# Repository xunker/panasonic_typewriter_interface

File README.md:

# Panasonic Typewriter Interface

https://github.com/xunker/panasonic_typewriter_interface

Print text using the Interface Port of your compatible Panasonic KX-R Daisywheel
typewriter, KX-W word processor, RK-T "CupWheel" typewriter, or KX-WD55
daisywheel printer. Emulates the serial/RS-232 function of the KX-R60 (currently
working), and RP-K100/RP-K105 (in development) interface adapters.

Use your 🏋️heavy🥌 and 🐢slow🐌 typewriter as a noisy, inconvenient, inflexible,
single-page printer!

A complete video of the ~~high~~ low-speed daisywheel action can be found on [the TouYubes](https://youtu.be/Eb-3h6uFz88).

## Table of Contents

- [Compatibility](#compatibility)
- [Typewriter Pinout](#typewriter-pinout)
- [Arduino Wiring](#arduino-wiring)
- [Code](#code)
- [Printerering (aka, how to use this)](#printerering-aka-how-to-use-this)
- [Serial Configuration Terminal](#serial-configuration-terminal)
- [Known Problems](#known-problems)
- [Theory of Operation](#theory-of-operation)
- [TODO](#todo)
- [License](#license)

## Compatibility

### KX-R series with MiniDIN-8 port

Developed and tested with my KX-R435, and should be compatible with any other
Panasonic typewriter with the round, 8-pin MiniDIN port.

### KX-W series with DE-9 port

Untested, but should work with machines which have a DE-9 (DB-9) connector.
**Currently does not work**, but is in active development. See
[rp-k10x_vs_kx-r60.md](./rp-k10x_vs_kx-r60.md) for research details.

## Typewriter Pinout

See [PINOUT.md](./PINOUT.md) for detailed information about the typewriter
connector pinout.

## Arduino Wiring

Although this is built around the Arduino Nano, any 5V board which uses the
ATmega328 will also work. Any other 5V ATmega MCU should work as as well (such
as the ATmega32U4in the Arduino Micro), and clones like the LGT8F328 (tested).

Non-ATmega/AVR boards *may* work, as long as they are compatible with the
libraries used in this project (see "Required Libraries"), have enough pins,
and run on 5V (or are 5V-tolerant). I have not tried any of this.

### Adapter Board

There's an [adapter board](adapter_boards/README.md) available to ease assembly,
and to provide additional features.

### Connecting Arduino to Typewriter without Adapter Board

Minimum required:

Arduino Pin | Goes To                | Purpose
------------|------------------------|--------
A0          | Typewriter ON_LINE pin | ~ON_LINE signal to typewriter
A1          | Typewriter TXD_PIN pin | TXD_PIN signal to typewriter
A2          | Typewriter STB_PIN pin | ~STB_PIN signal to typewriter
A3          | Typewriter ACK_PIN pin | ~ACK_PIN signal from typewriter
A6          | Switch to ground       | "RUN/HALT" switch (GO_PIN), active low

Optional "Mode" button:

Arduino Pin | Goes To          | Purpose
------------|------------------|--------
A7          | Button to ground | Mode button (MODE_PIN), optional, active low

Separate USB-to-Serial Adapter: You can use the built-in USB port as the Serial
connection, but hardware flow control will not be available. To use hardware
flow control you will need to connect up to an external USB to Serial adapter:

Arduino Pin | Goes To                  | Purpose
------------|--------------------------|--------
TX1 (D1)    | RxD on USB Serial Module | Transmit serial data to USB host
RX0 (D0)    | TxD on USB Serial Module | Receive serial data from USB host
11          | CTS on USB Serial module | CTS (Clear to Send)
12          | RTS on USB Serial module | RTS (Request to Send)

You can also connect some optional additional LEDs for debugging (or because
they look neat when they blink):

Arduino Pin | Goes To | Purpose
------------|---------|--------
8           | LED +   | State of ON_LINE pin
6           | LED +   | State of STB_LED pin
2           | LED +   | State of ACK_LED pin
3           | LED +   | State of TXD_LED pin

## Code

The included code will read data from the `Serial` device (usually USB Serial)
and relay that to the typewriter in the correct format.

### Required Libraries

The following libraries are required by default. They can either be installed
manually or via the Arduino IDE:

* [SerialCmd](https://github.com/gpb01/SerialCmd)
* [MemoryUsage](https://github.com/Locoduino/MemoryUsage)
* [AceButton](https://github.com/bxparks/AceButton/)

SerialCmd and MemoryUsage are only needed by the
[Serial Configuration Terminal](./SERIAL_CONFIG.md) (enabled default). AceButton
is only needed if the "Mode" button is enabled (enabled by default).

### Configure

NOTE: if you are using the included [adapter board](adapter_boards/README.md), you do not need to do any
additional configuration. Simply connect your cable and adjust the "Cable Type"
jumpers so they are both closest to whichever LED (D1 or D2) is lit up.

Edit [panasonic_typewriter_interface.ino](./panasonic_typewriter_interface.ino)
and change the following lines as appropriate:

```c
#define ON_LINE_PIN A0 // Output, active LOW
#define STB_PIN     A2 // Output, active LOW
#define ACK_PIN     A3 // Input, active LOW
#define TXD_PIN     A1 // Output; HIGH = 1, LOW = 0

#define GO_PIN      A6 // trigger printing to begin when this is pulled low

#define MODE_PIN    A7 // trigger printing to begin when this is pulled low

/* RTS_PIN/CTS_PIN are only needed if `#define ENABLE_RTS_CTS` is uncommented */
#define RTS_PIN 12 // incoming from RTS, active low (for ENABLE_RTS_CTS)
#define CTS_PIN 11 // outgoing to CTS, active low   (for ENABLE_RTS_CTS)
```

CHECK WHAT KIND OF CABLE YOU HAVE, and remember that a Macintosh-style printer
cable likely has several pins swapped.

Once you're done, upload it to your Arduino-compatible MCU.

There is also a "Demo Mode" that will just print text automatically and not
wait for input over serial; enable that by uncommenting `// #define TEST_MODE`
in panasonic_typewriter_interface.ino.

#### Extra LEDs (Optional, default)

By default, there are 4 addition LEDs broken out to show the status of each of
the signal lines (in addition to the built-in LED).

```c
#define ON_LINE_LED 8
#define STB_LED     6
#define ACK_LED     2
#define TXD_LED     3
#define LED_BUILTIN 13 // "Status" LED
```

These LEDs will reflect the _state_ of each respective signal.
Note, this is a _logic state_, not the _electrical state_. That means for
active-low pins like ON_LINE, STB, and ACT, a low signal will turn *on* the
appropriate LED.

However, if you do not require these additional LEDs you can comment-out the
line `#define ENABLE_MULTIPLE_LEDS`, and then only the built-in LED will be
used.

## Printerering (aka, how to use this)

Once the code is uploaded and your Arduino is properly connected to your
typewriter, turn on your typewriter and load paper as appropriate.

### Set Typewriter to "On-Line Mode"

Then, you must get in to "On-Line Mode". The command varies from model to model,
so consult the owners manual for more detail. In the case of the KX-R435, you
enter On-Line Mode by holding down the `CODE` key and then pressing `E`; the LCD
should now say "On-Line Mode". To exit On-Line mode, or to stop printing, press
CODE+E again.

### Set microcontroller to "RUN" Mode

Once in "On-Line Mode", you'll need to set your Arduino to "Run" mode. If you
are using the included [adapter board](adapter_boards/README.md), you do this by
switching the "RUN/HALT" switch to "RUN". If you are have wired your own
microcontroller, you will connect pin A7 (or whatever pin you assigned to
`GO_PIN`) to ground.

Once you switch to "RUN" mode, reset the microcontroller once to ensure it's now
in the correct mode.

As long as that pin is grounded, sentences will keep being sent to the
typewriter.

### Send text - SLOWLY

Finally, open a serial connection to your MCU (using the built-in Serial Console
in the Arduino IDE works well).

The default speed is 300 baud. Yes, you read correctly, **300 baud**. Because
it's a freakin' TYPEWRITER! It can _barely_ keep up with 30 char/sec. If you
want a laser printer, you know where to find one.

Out of the box, the Arduino toolchain only gives the atMega328 a 64 byte serial
buffer, which can hold about 2 seconds of data at 300 baud. I'd actually like
to set the default speed to 110 baud, but no operating systems have supported
that speed for at least 30 years. Yes, not even Linux despite the lies that
`stty` tells you.

Send some text! With luck, you'll see it appear in your paper! Eventually!

## Serial Configuration Terminal

See [SERIAL_CONFIG.md](./SERIAL_CONFIG.md).

## Known Problems

### Can't keep up with 300 baud without hardware flow control

The default speed is 300 baud (see "Send text - SLOWLY" for reasons), and even
that has problems unless you use hardware flow control (RTS/CTS) and text will
start to be dropped in about 2 lines.

This is because of two things issues:
* the Arduino Serial buffer is
  [only 64 bytes](https://docs.arduino.cc/language-reference/en/functions/communication/serial/available/),
  on the ATmega328
* Even the fastest Panasonic Daisywheels can only print 15 characters/sec, which is
  only half the speed of 300 baud, and most models can only print 12 CPS

There are two solutions:
* Use hardware flow control
  - On USB, this requires use of a *separate* USB-to-Serial adapter because the
    IC included on Arduino Nano does *not* connect any lines besides TxD, RxD,
    and DTR
  - The current Adapter Board can use a separate USB-to-Serial adapter connected
    to J4, with CTS connexted to "TX1" and RTC connected to "RX1"
  - Future versions of the adapter board will include footprints for a separate
    USB-to-serial converter
* add a "character delay" when you send, greater than 30ms/character
  - CoolTerm can do this: `Options`->`Transmit`->`Use Transmit Character Delay`

### Reboot required when switching from from HALT to RUN with Serial Console

If [Serial Console](./SERIAL_CONFIG.md) support is compiled in (the default), a reboot (via reset
button) is require when going from HALT mode to RUN mode.

### Mode button doesn't do anything

The "[Mode Button](./mode_button.h)" is currently GN/DN (goes nowhere & does nothing).

## Theory of Operation

See [rp-k10x_vs_kx-r60.md](./rp-k10x_vs_kx-r60.md) for a detailed sequence diagram.

## TODO

### Need
Rough order of importance:

* Working emulation of [RP-K100 and RP-K105](./rp-k10x_vs_kx-r60.md) adapters
* Use .h files properly; move code out of those
* Finish V2 adapter board which will give RTS/CTS and RS-232 options
  - must get RP-K100 and RP-K105 workign first
* Get special/accented character conversion functioning
* Convert special characters like tab ("\t") to spaces, to prevent typewriter from going crazy if no tabs have been set
  - ability to set tab-to-space count in serial console

### Want
In no particular order:
* DTR/DSR support, for compatibility with older hosts that didn't use RTS/CTS
  - Ex: Apple II, C64, TRS80, etc.
* Transceivers or driver/receiver pairs for typewriter connection, for buffering
  and for possible 3.3v operation
  - 3x active-low drivers
  - 1x active-low receiver
* Better serial buffering
  * Default 64 byte buffer doesn't even do 300 baud well
  * Implement a 1K ring buffer? We have the free SRAM
  * This is less of an issue with RTS/CTS support
* Support alt Serial on LGT8F328 with Rx/Tx pins 5 & 6
* Separate serial interface for debugging output on different pins, with different baud rate
  * Software serial, or SERIAL1 on 328PB or LGT8F328
* I2C display support
  - in software, alreadu have hardware support via Stemma connector
* Automatically insert correct line-breaks, depending on CPI switch setting
  - May not be needed or even supported
    * Windows' generic/text only printer [automatically wraps at 80 characters](https://support.microsoft.com/en-us/topic/printing-wide-carriage-with-generic-text-only-print-driver-3bdb3c49-abdd-597d-6416-5d460efab182)
* Automatically pause printing to insert next sheet of paper, based on line-spacing switch setting
  * MODE button becomes "Continue" button
* mode button cycles through CPI/Line Space settings? Need display for this?

## License

[GNU GPL 3](LICENSE)

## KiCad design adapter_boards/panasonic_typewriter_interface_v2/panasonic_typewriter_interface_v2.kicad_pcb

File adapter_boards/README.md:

# Adapter Board for Panasonic Typewriter Interface

https://github.com/xunker/panasonic_typewriter_interface

[![Back of
PCB](pcb_2024-10-a_back_small.jpg)](pcb_2024-10-a_back.png)

Here is an adapter board to make it easier to wire up your typewriter. It's
based ardound the Arduino Nano, and will work with compatible clones like
LGT8F328.

## Important note about Hardware Flow Control

This version of the board (marked "Rev 2024-10-A") does not support Hardware
Flow Control (RTS/CTS or DTR/DSR) without additional components.

You CAN still use this design without flow control as long as you are able to
add a ~30-50 millisecond-per-character delay to your transmission, or reduce
the Baud Rate to 150 or 110.

CoolTerm, for example has the option to add this per-character delay.

To add hardware flow control to this design, you need to use an external
USB-to-Serial adapter which has connections for RTS/CTS and/or DTR/DSR.

You can connect the external USB-to-Serial to this board via connector J4 on the
bottom of the board, and use pin labeld "RX1" as RTS and "TX1" as CTS. "TX0"
and "RX0" be be used as TxD and RxD respectively.

J4 is a surface-mount footprint for a JST GH connector (1.25mm) but a Molex
PicoBlade (also sold as "JST Micro" connector) will also fit. You can also
solder wires directly to the pads, or use a piece of 1.27mm break-away header
to build your own conenctor.

### Voltage Warning

Some "Nano" clone modules might be 3.3V instead of 5V. This board will **only
work with 5V models**, and a **3.3V model will get fried** if you use one here!

## Features

In addition to connecting your typewriter to the microcontroller, this board
also has some extra benefits:

### Cable Type Detection and Selection

When you connected to a KX-R typewriter, this board will tell you the kind of
cable you are using (straight or cross-over) and gives you a simple way to
configure the board for it.

When the connected typewriter is turned on, either LED D1 or D2 should turn on.
Move the two jumpers on J2 to the side closest to whatever LED is lit.

### Separate Signal LEDs

LED D3 is a duplicate of the built-in LED on the Arduino Nano, and is used
as a general-purpose "status" LED.

LEDs D4-D7 show the state of the signals to and from the typewriter. This can
help when troubleshooting connection problems.

### Raw Typewriter Signal Breakout

Connector J3, 6-pin JST GH, can use used to access the raw (unbuffered) signals
going to and from the typewriter.

### Arduino Serial Breakout

Conenctor J4, 6-pin JST GH, can use used to access the TTL-level Serial signals
from the Arduino Nano.

#### Second Serial Breakout ('328PB)

If your module is using the atMega328PB MCU (only used in clones), this board
also gives you access to the second serial device (`Serial1`).

### I2C Breakout

Conenctor J5, 4-pin JST SH, provides a connection for I2C and is compatible
with the "Stemma QT" connector standard used by AdaFruit and Sparkfun.

## Files

Files for this board can be found in
[panasonic_typewriter_interface](./panasonic_typewriter_interface).

## Bill of Materials

Qty | Name                       | ID     | Notes
----|----------------------------|--------|-----------------------------------
1   | Arduino Nano or compatible | A1     | If using a clone, ensure 5V model
7   | 0805 SMD LED               | D1-D7  | any LED of correct size will do
1   | 2x06 SMD Header, 2.54mm    | J2     |
2   | Jumpers/Shunts for J2      | n/a    |
1   | MiniDIN-8 connector        | J1     | KMDGX-8S-AS, but most others work
2   | 0805 1.2K ohm Resistor     | R1, R2 |
5   | 0805 220-330ohm Resistor   | R3-R7  |
1   | PCM12 Switch, SMD SPDT     | SW1    |
1   | FSMSM Button               | SW2    |
1   | 1206 Fuse, SMD, <500mA     | F1     | Optional
2   | JST GH Connector, 6-pin    | J3, J4 | Optional
1   | JST SH Connector, 4-pin    | J5     | Optional

## License

This board is published under the terms of the
[Creative Commons Attribution-NonCommercial-ShareAlike 4.0
International](https://creativecommons.org/licenses/by-nc-sa/4.0/deed.en) license.

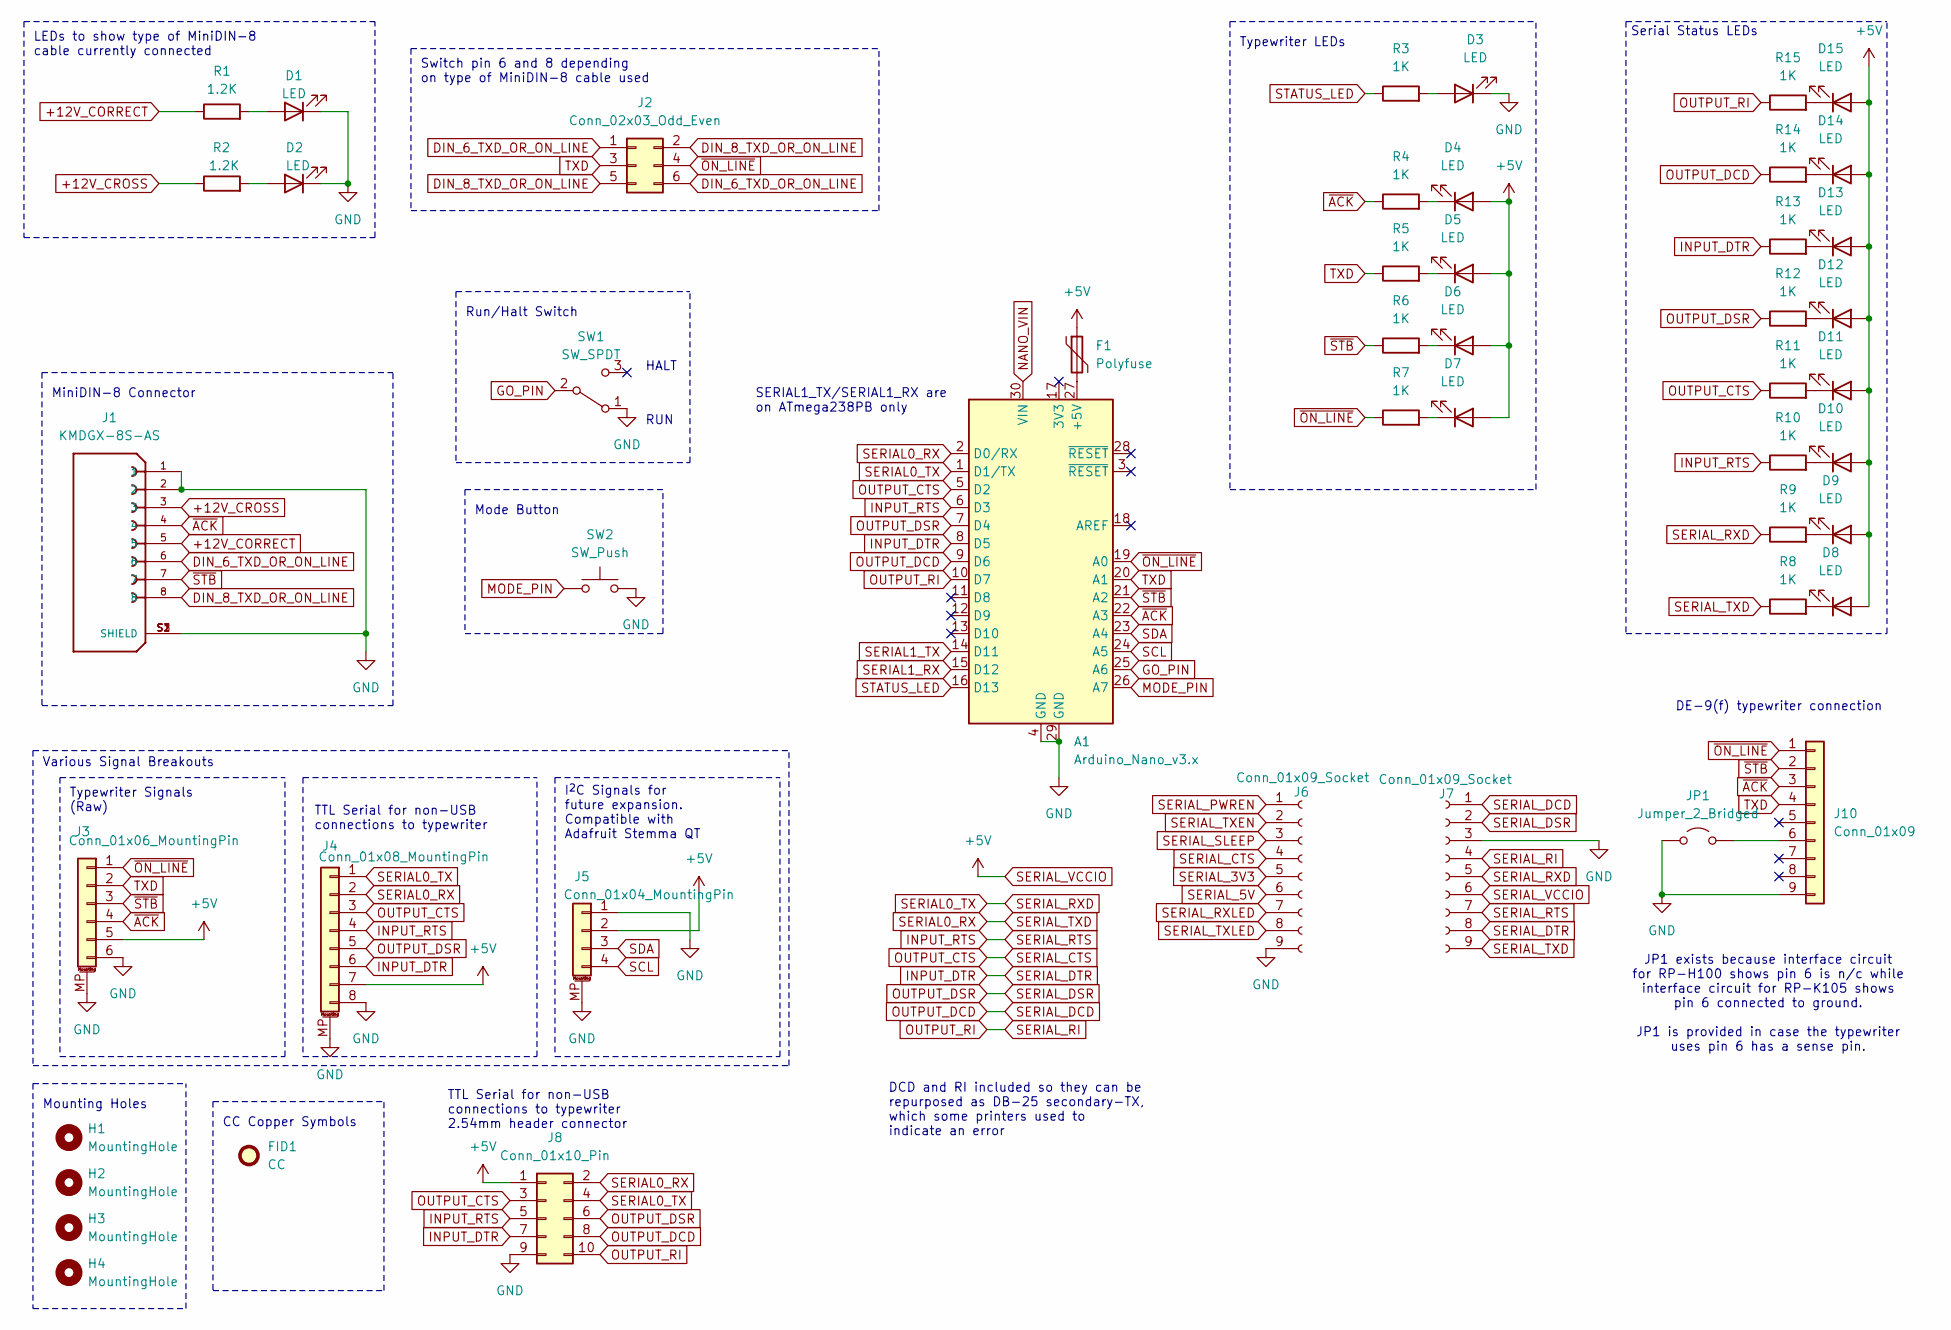
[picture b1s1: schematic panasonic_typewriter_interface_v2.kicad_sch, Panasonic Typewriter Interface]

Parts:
A1: Arduino_Nano_v3.x; Arduino_Nano
D1, D2, D3, D4, D5, D6, D7, D8, D9, D10, D11, D12, D13, D14, D15: LED; LED_0805_2012Metric
F1: Polyfuse; Fuse_1206_3216Metric
FID1: CC; Symbol_CreativeCommons_CopperTop_Type2_Small
H1, H2, H3, H4: MountingHole; MountingHole_2.2mm_M2_DIN965
J1: KMDGX-8S-AS; KYCON_KMDGX-8S-AS; PARTREV C6
J2: Conn_02x03_Odd_Even; PinHeader_2x03_P2.54mm_Vertical_SMD
J3: Conn_01x06_MountingPin; Molex_PicoBlade_53261-0671_1x06-1MP_P1.25mm_Horizontal
J4: Conn_01x08_MountingPin; Molex_PicoBlade_53261-0871_1x08-1MP_P1.25mm_Horizontal
J5: Conn_01x04_MountingPin; JST_SH_SM04B-SRSS-TB_1x04-1MP_P1.00mm_Horizontal
J6, J7: Conn_01x09_Socket; PinSocket_1x09_P2.54mm_Vertical
J8: Conn_01x10_Pin; PinHeader_2x05_P2.54mm_Vertical
J10: Conn_01x09; DSUB-9_Female_EdgeMount_P2.77mm
JP1: Jumper_2_Bridged; SolderJumper-2_P1.3mm_Open_RoundedPad1.0x1.5mm
R1, R2: 1.2K; R_0805_2012Metric
R3, R4, R5, R6, R7, R8, R9, R10, R11, R12, R13, R14, R15: 1K; R_0805_2012Metric
SW1: SW_SPDT; SW_SPDT_PCM12
SW2: SW_Push; SW_SPST_FSMSM

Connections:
+12V_CORRECT: J1.5, R1.1
+12V_CROSS: J1.3, R2.1
DIN_6_TXD_OR_ON_LINE: J1.6, J2.1, J2.6
DIN_8_TXD_OR_ON_LINE: J1.8, J2.2, J2.5
GND: A1.4 (GND), A1.29 (GND), D1.1 (K), D2.1 (K), D3.1 (K), J1.1, J1.2, J1.S1 (SHIELD), J1.S2 (SHIELD), J1.S3 (SHIELD), J3.6, J3.MP (MountPin), J4.8, J4.MP (MountPin), J5.1, J5.MP (MountPin), J6.9, J7.3, J8.9, J10.9, JP1.1 (A), SW1.1 (A), SW2.1
GO_PIN: A1.25 (A6), SW1.2 (B)
INPUT_DTR: A1.8 (D5), J4.6, J7.8, J8.7, R13.1
INPUT_RTS: A1.6 (D3), J4.4, J7.7, J8.5, R10.1
MODE_PIN: A1.26 (A7), SW2.2
NANO_VIN: A1.30 (VIN)
unnamed: A1.27 (+5V), F1.2
unnamed: D1.2 (A), R1.2
unnamed: D2.2 (A), R2.2
unnamed: D3.2 (A), R3.2
unnamed: D4.1 (K), R4.2
unnamed: D5.1 (K), R5.2
unnamed: D6.1 (K), R6.2
unnamed: D7.1 (K), R7.2
unnamed: D8.1 (K), R8.2
unnamed: D9.1 (K), R9.2
unnamed: D10.1 (K), R10.2
unnamed: D11.1 (K), R11.2
unnamed: D12.1 (K), R12.2
unnamed: D13.1 (K), R13.2
unnamed: D14.1 (K), R14.2
unnamed: D15.1 (K), R15.2
unnamed: J10.6, JP1.2 (B)
OUTPUT_CTS: A1.5 (D2), J4.3, J6.4, J8.3, R11.1
OUTPUT_DCD: A1.9 (D6), J7.1, J8.8, R14.1
OUTPUT_DSR: A1.7 (D4), J4.5, J7.2, J8.6, R12.1
OUTPUT_RI: A1.10 (D7), J7.4, J8.10, R15.1
SCL: A1.24 (A5), J5.4
SDA: A1.23 (A4), J5.3
SERIAL0_RX: A1.2 (D0/RX), J4.2, J7.9, J8.2, R8.1
SERIAL0_TX: A1.1 (D1/TX), J4.1, J7.5, J8.4, R9.1
SERIAL1_RX: A1.15 (D12)
SERIAL1_TX: A1.14 (D11)
SERIAL_3V3: J6.5
SERIAL_5V: J6.6
SERIAL_PWREN: J6.1
SERIAL_RXLED: J6.7
SERIAL_SLEEP: J6.3
SERIAL_TXEN: J6.2
SERIAL_TXLED: J6.8
SERIAL_VCCIO: D4.2 (A), D5.2 (A), D6.2 (A), D7.2 (A), D8.2 (A), D9.2 (A), D10.2 (A), D11.2 (A), D12.2 (A), D13.2 (A), D14.2 (A), D15.2 (A), F1.1, J3.5, J4.7, J5.2, J7.6, J8.1
STATUS_LED: A1.16 (D13), R3.1
TXD: A1.20 (A1), J2.3, J3.2, J10.4, R5.1
~ACK: A1.22 (A3), J1.4, J3.4, J10.3, R4.1
~ON_LINE: A1.19 (A0), J2.4, J3.1, J10.1, R7.1
~STB: A1.21 (A2), J1.7, J3.3, J10.2, R6.1

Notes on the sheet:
Switch pin 6 and 8 depending on type of MiniDIN-8 cable used
JP1 exists because interface circuit for RP-H100 shows pin 6 is n/c while interface circuit for RP-K105 shows pin 6 connected to ground. JP1 is provided in case the typewriter uses pin 6 has a sense pin.
LEDs to show type of MiniDIN-8 cable currently connected
HALT
Typewriter LEDs
Run/Halt Switch
Serial Status LEDs
RUN
Mounting Holes
DCD and RI included so they can be repurposed as DB-25 secondary-TX, which some printers used to indicate an error
CC Copper Symbols
Mode Button
I^{2}C Signals for future expansion. Compatible with Adafruit Stemma QT
MiniDIN-8 Connector
TTL Serial for non-USB connections to typewriter 2.54mm header connector
Various Signal Breakouts
TTL Serial for non-USB connections to typewriter
DE-9(f) typewriter connection
SERIAL1_TX/SERIAL1_RX are on ATmega238PB only
Typewriter Signals (Raw)

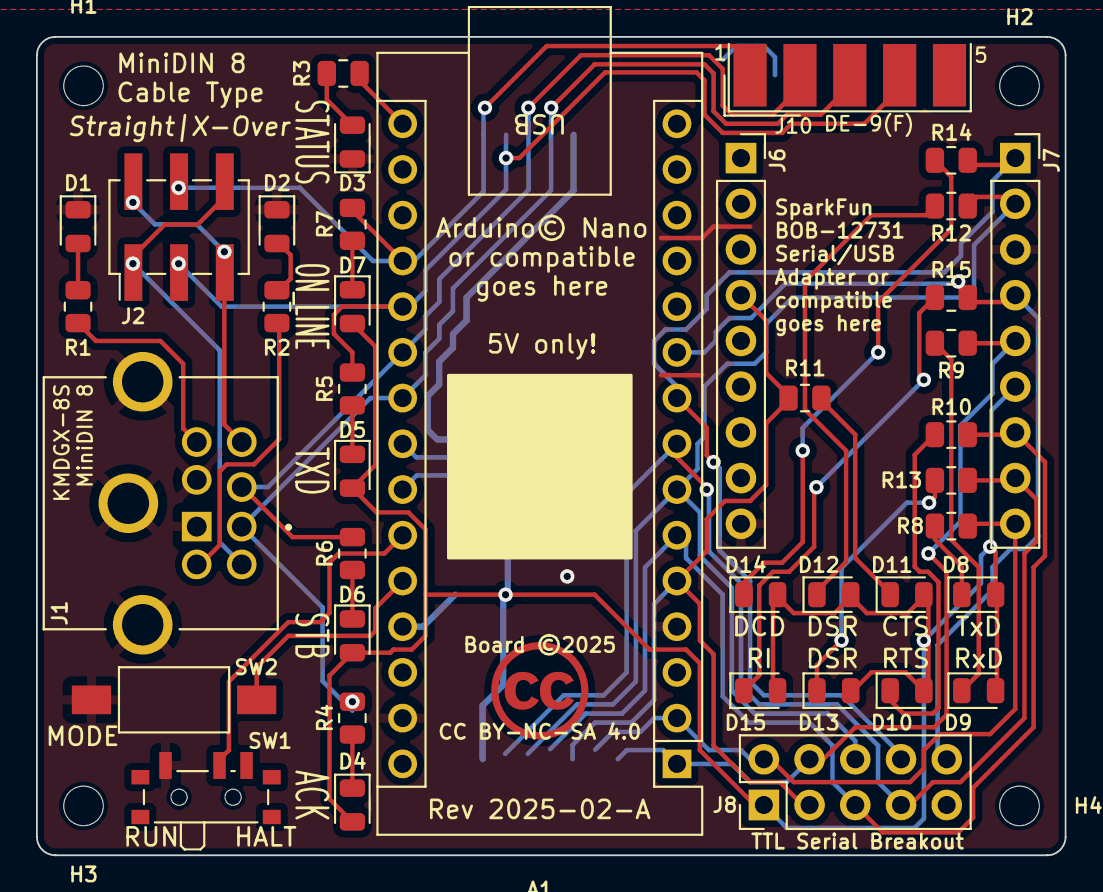
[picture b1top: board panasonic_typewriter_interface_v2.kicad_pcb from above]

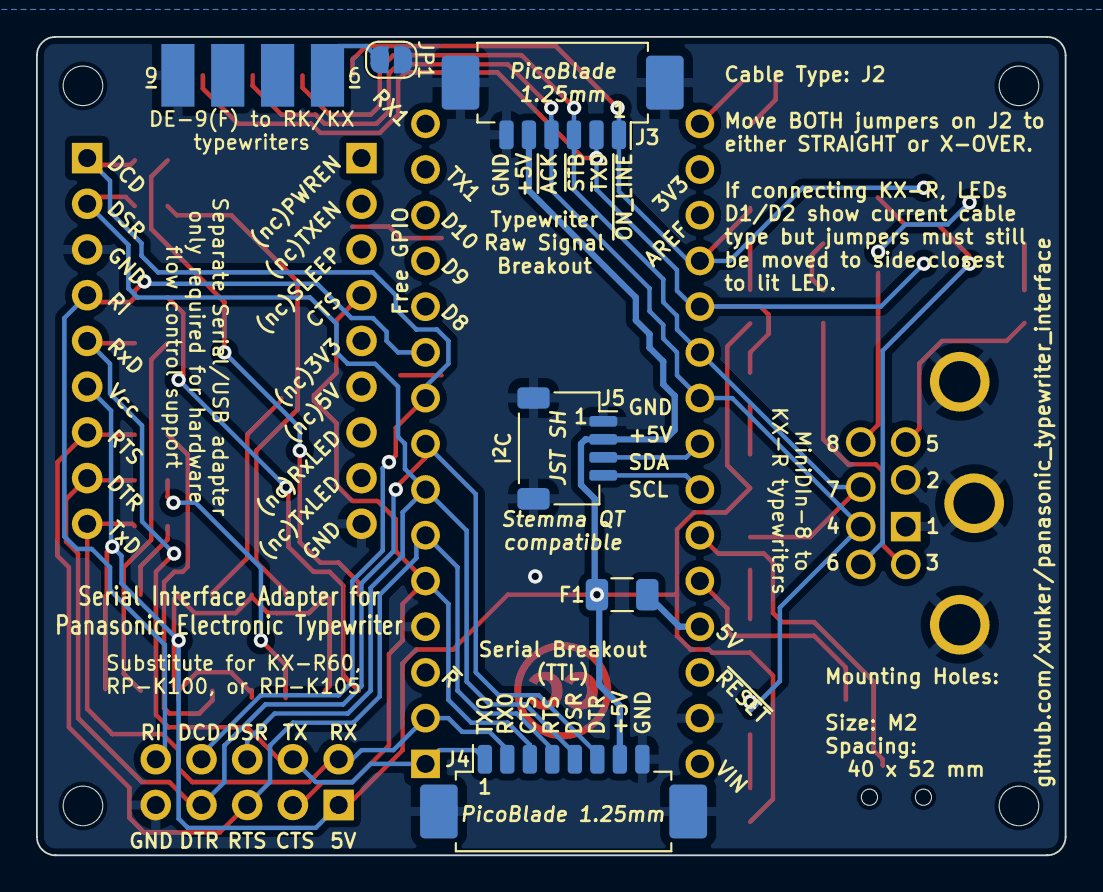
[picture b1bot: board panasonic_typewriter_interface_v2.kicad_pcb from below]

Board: 2 copper layers, 57.2 x 45.5 mm, 49 parts (5 on the bottom side), 40 nets.

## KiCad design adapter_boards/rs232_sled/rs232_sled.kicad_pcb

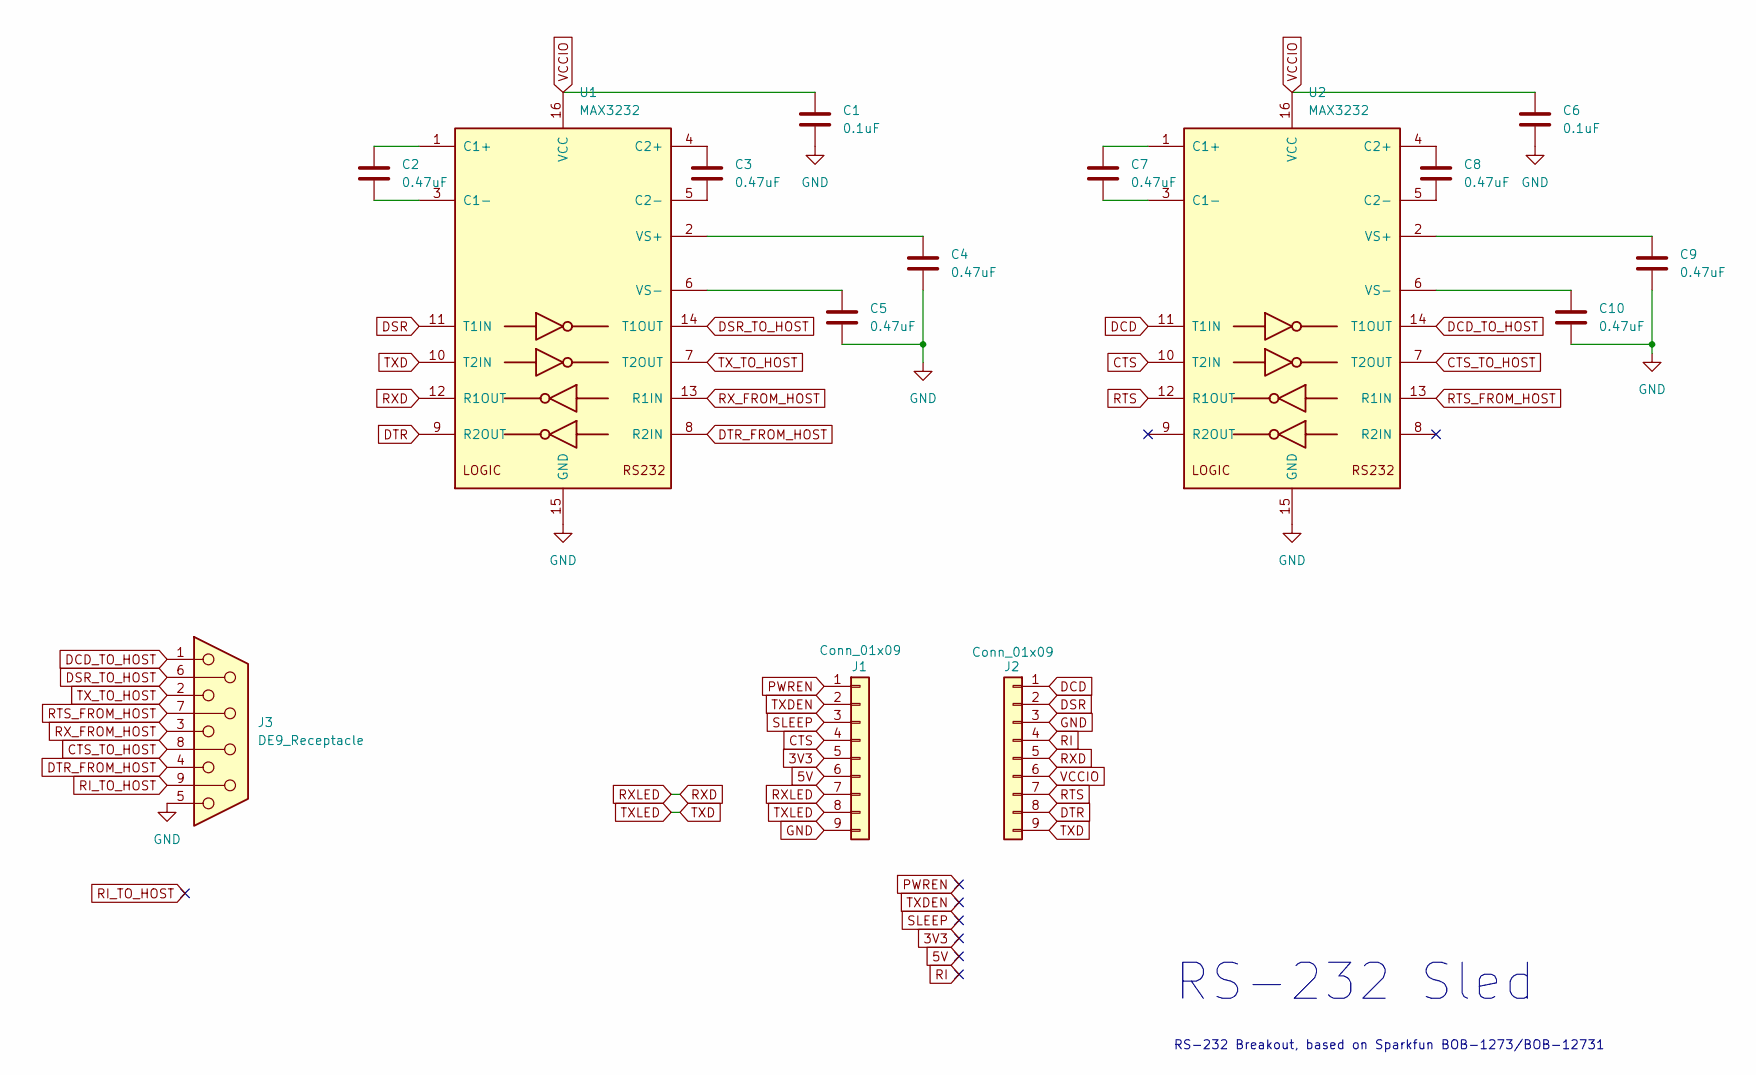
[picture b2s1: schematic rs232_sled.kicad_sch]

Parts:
C1, C6: 0.1uF; C_0603_1608Metric
C2, C3, C4, C5, C7, C8, C9, C10: 0.47uF; C_0603_1608Metric
J1, J2: Conn_01x09; PinHeader_1x09_P2.54mm_Vertical
J3: DE9_Receptacle; DSUB-9_Female_EdgeMount_P2.77mm
U1, U2: MAX3232; SOIC-16_4.55x10.3mm_P1.27mm

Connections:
3V3: J1.5
5V: J1.6
CTS: J1.4, U2.10 (T2IN)
CTS_TO_HOST: J3.8, U2.7 (T2OUT)
DCD: J2.1, U2.11 (T1IN)
DCD_TO_HOST: J3.1, U2.14 (T1OUT)
DSR: J2.2, U1.11 (T1IN)
DSR_TO_HOST: J3.6, U1.14 (T1OUT)
DTR: J2.8, U1.9 (R2OUT)
DTR_FROM_HOST: J3.4, U1.8 (R2IN)
GND: C1.2, C4.2, C5.2, C6.2, C9.2, C10.2, J1.9, J2.3, J3.5, U1.15 (GND), U2.15 (GND)
unnamed: C2.1, U1.1 (C1+)
unnamed: C2.2, U1.3 (C1-)
unnamed: C3.1, U1.4 (C2+)
unnamed: C3.2, U1.5 (C2-)
unnamed: C4.1, U1.2 (VS+)
unnamed: C5.1, U1.6 (VS-)
unnamed: C7.1, U2.1 (C1+)
unnamed: C7.2, U2.3 (C1-)
unnamed: C8.1, U2.4 (C2+)
unnamed: C8.2, U2.5 (C2-)
unnamed: C9.1, U2.2 (VS+)
unnamed: C10.1, U2.6 (VS-)
PWREN: J1.1
RI: J2.4
RI_TO_HOST: J3.9
RTS: J2.7, U2.12 (R1OUT)
RTS_FROM_HOST: J3.7, U2.13 (R1IN)
RXD: J1.7, J2.5, U1.12 (R1OUT)
RX_FROM_HOST: J3.3, U1.13 (R1IN)
SLEEP: J1.3
TXD: J1.8, J2.9, U1.10 (T2IN)
TXDEN: J1.2
TX_TO_HOST: J3.2, U1.7 (T2OUT)
VCCIO: C1.1, C6.1, J2.6, U1.16 (VCC), U2.16 (VCC)

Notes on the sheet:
RS-232 Breakout, based on Sparkfun BOB-1273/BOB-12731
RS-232 Sled

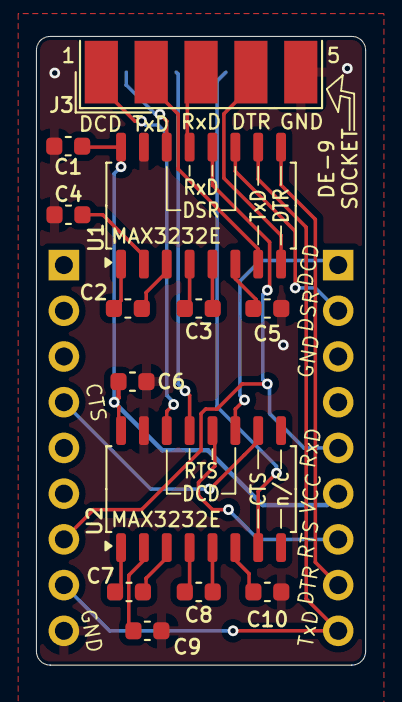
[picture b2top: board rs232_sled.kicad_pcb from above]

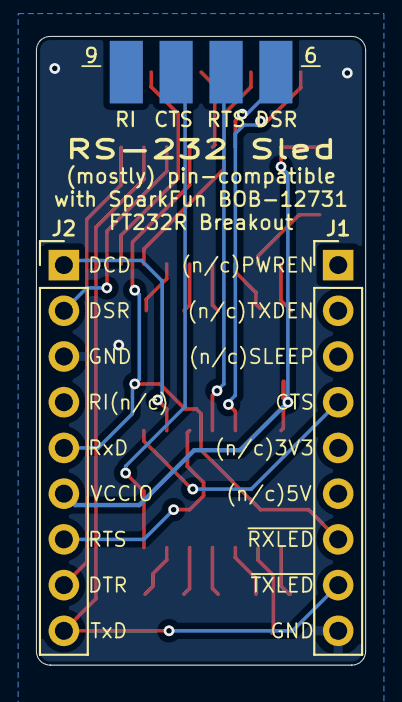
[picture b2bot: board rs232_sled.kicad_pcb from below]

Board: 2 copper layers, 18.3 x 34.9 mm, 15 parts (2 on the bottom side), 28 nets.

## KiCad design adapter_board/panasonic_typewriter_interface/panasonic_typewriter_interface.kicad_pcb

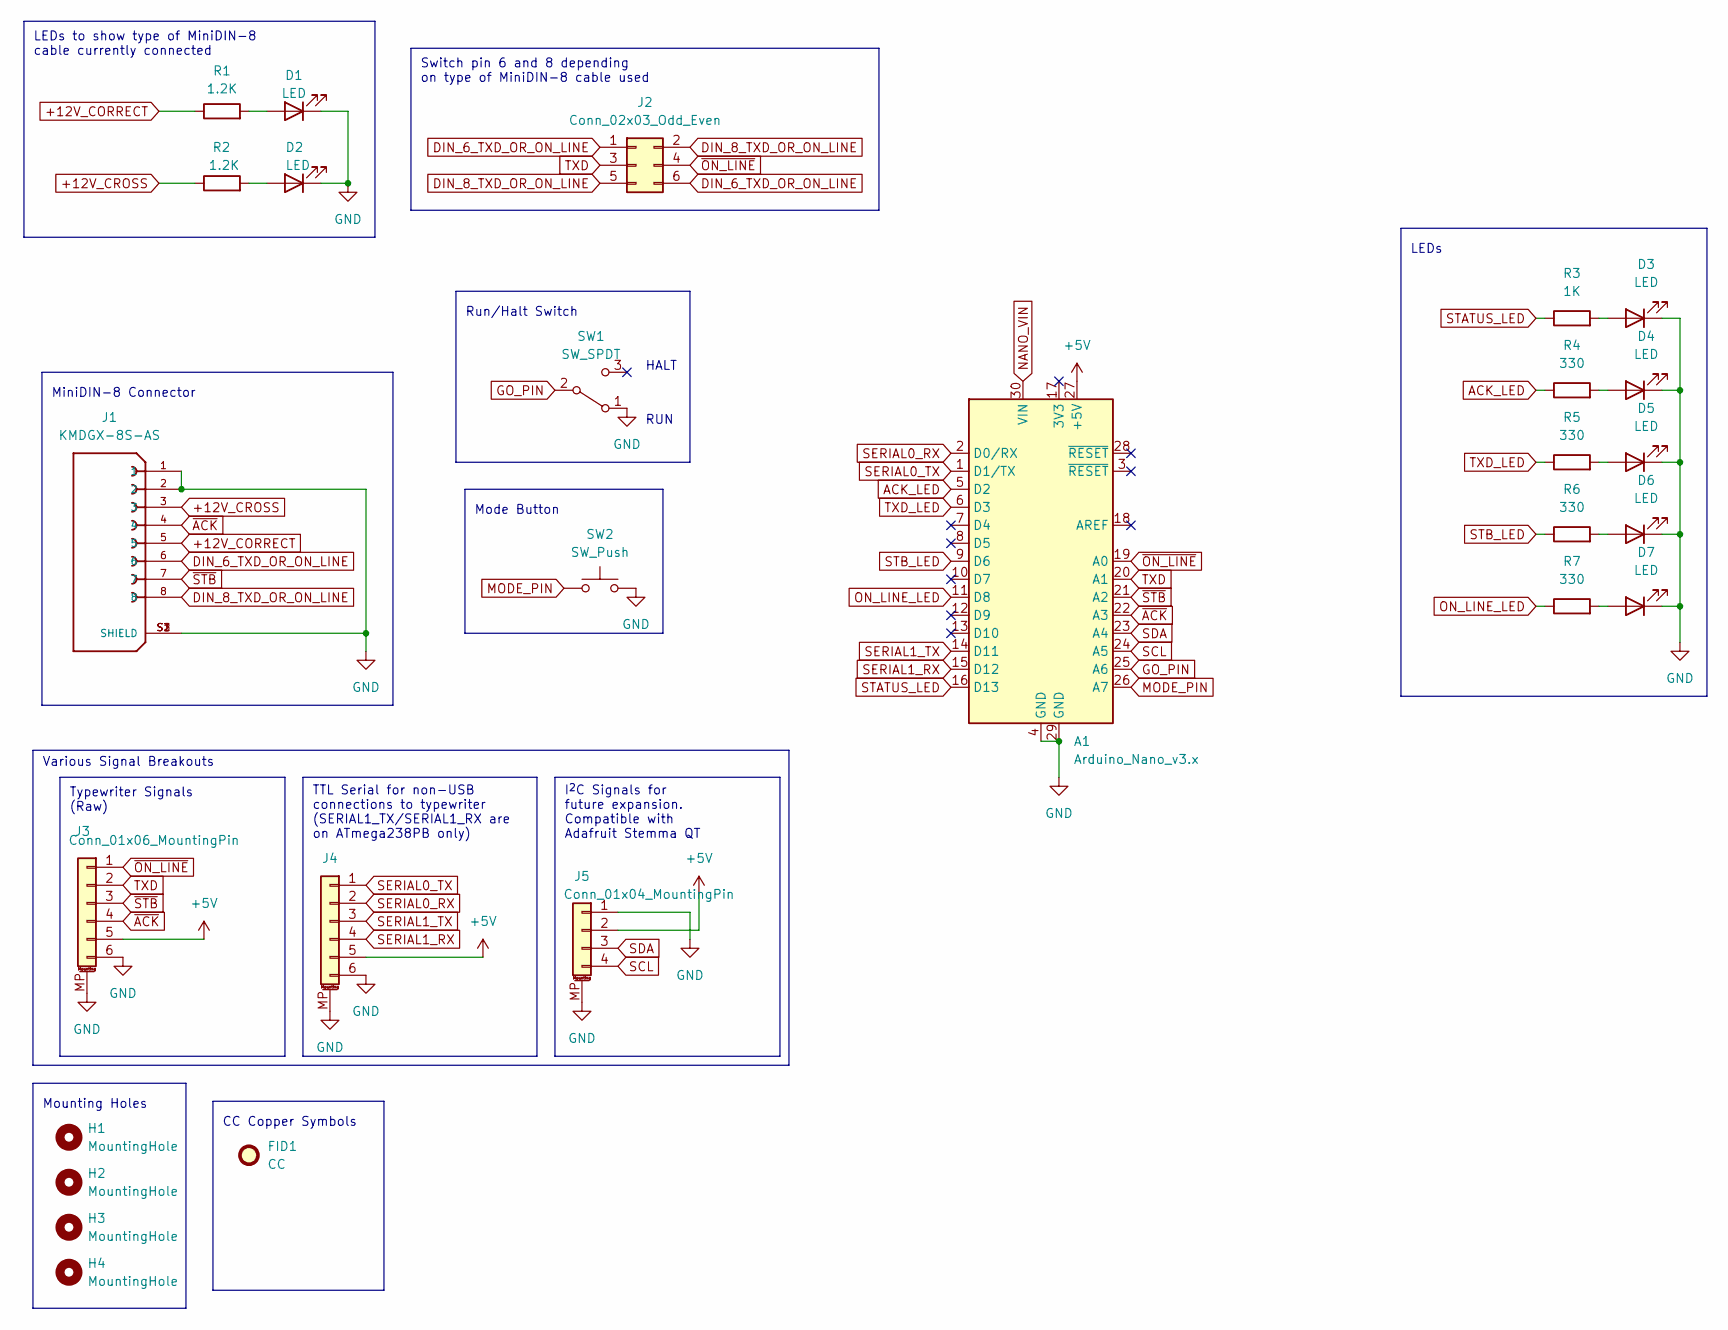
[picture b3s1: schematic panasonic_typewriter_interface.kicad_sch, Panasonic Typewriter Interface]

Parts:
A1: Arduino_Nano_v3.x; Arduino_Nano
D1, D2, D3, D4, D5, D6, D7: LED; LED_0805_2012Metric
FID1: CC; Symbol_CreativeCommons_CopperTop_Type2_Small
H1, H2, H3, H4: MountingHole; MountingHole_2.2mm_M2_DIN965
J1: KMDGX-8S-AS; KYCON_KMDGX-8S-AS; PARTREV C6
J2: Conn_02x03_Odd_Even; PinHeader_2x03_P2.54mm_Vertical_SMD
J3: Conn_01x06_MountingPin
J4: (no value)
J5: Conn_01x04_MountingPin; JST_SH_SM04B-SRSS-TB_1x04-1MP_P1.00mm_Horizontal
R1, R2: 1.2K; R_0805_2012Metric
R3: 1K; R_0805_2012Metric
R4, R5, R6, R7: 330; R_0805_2012Metric
SW1: SW_SPDT; SW_SPDT_PCM12
SW2: SW_Push; SW_SPST_FSMSM

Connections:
+5V: A1.27 (+5V), J3.5, J4.5, J5.2
+12V_CORRECT: J1.5, R1.1
+12V_CROSS: J1.3, R2.1
ACK_LED: A1.5 (D2), R4.1
DIN_6_TXD_OR_ON_LINE: J1.6, J2.1, J2.6
DIN_8_TXD_OR_ON_LINE: J1.8, J2.2, J2.5
GND: A1.4 (GND), A1.29 (GND), D1.1 (K), D2.1 (K), D3.1 (K), D4.1 (K), D5.1 (K), D6.1 (K), D7.1 (K), J1.1, J1.2, J1.S1 (SHIELD), J1.S2 (SHIELD), J1.S3 (SHIELD), J3.6, J3.MP (MountPin), J4.6, J4.MP (MountPin), J5.1, J5.MP (MountPin), SW1.1 (A), SW2.1
GO_PIN: A1.25 (A6), SW1.2 (B)
MODE_PIN: A1.26 (A7), SW2.2
NANO_VIN: A1.30 (VIN)
unnamed: D1.2 (A), R1.2
unnamed: D2.2 (A), R2.2
unnamed: D3.2 (A), R3.2
unnamed: D4.2 (A), R4.2
unnamed: D5.2 (A), R5.2
unnamed: D6.2 (A), R6.2
unnamed: D7.2 (A), R7.2
ON_LINE_LED: A1.11 (D8), R7.1
SCL: A1.24 (A5), J5.4
SDA: A1.23 (A4), J5.3
SERIAL0_RX: A1.2 (D0/RX), J4.2
SERIAL0_TX: A1.1 (D1/TX), J4.1
SERIAL1_RX: A1.15 (D12), J4.4
SERIAL1_TX: A1.14 (D11), J4.3
STATUS_LED: A1.16 (D13), R3.1
STB_LED: A1.9 (D6), R6.1
TXD: A1.20 (A1), J2.3, J3.2
TXD_LED: A1.6 (D3), R5.1
~ACK: A1.22 (A3), J1.4, J3.4
~ON_LINE: A1.19 (A0), J2.4, J3.1
~STB: A1.21 (A2), J1.7, J3.3

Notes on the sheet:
Switch pin 6 and 8 depending on type of MiniDIN-8 cable used
LEDs to show type of MiniDIN-8 cable currently connected
HALT
LEDs
Run/Halt Switch
RUN
Mounting Holes
CC Copper Symbols
Mode Button
I^{2}C Signals for future expansion. Compatible with Adafruit Stemma QT
MiniDIN-8 Connector
Various Signal Breakouts
TTL Serial for non-USB connections to typewriter (SERIAL1_TX/SERIAL1_RX are on ATmega238PB only)
Typewriter Signals (Raw)

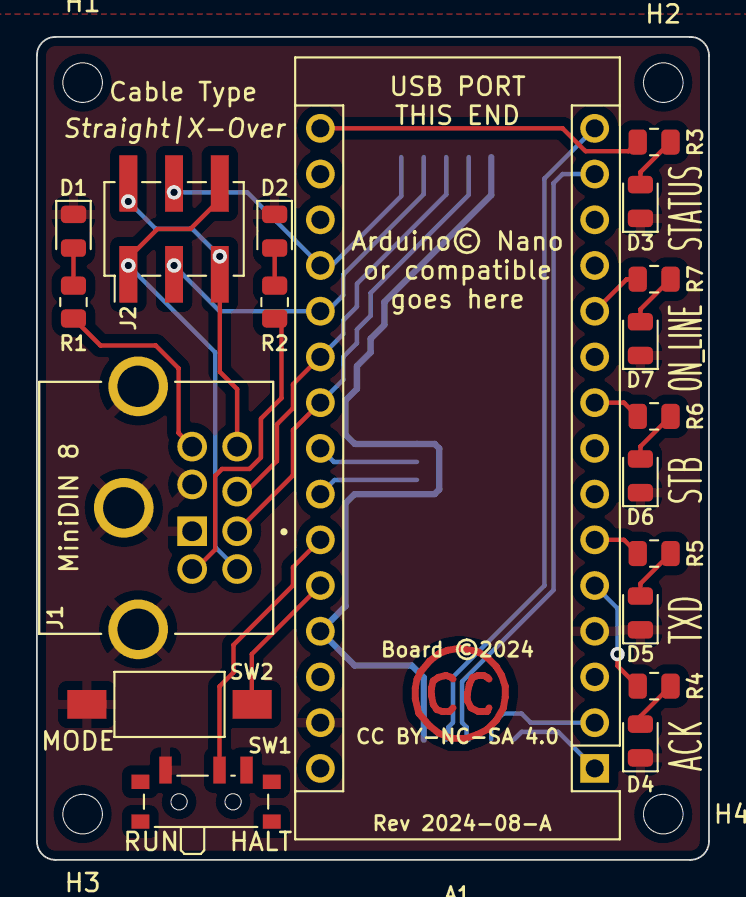
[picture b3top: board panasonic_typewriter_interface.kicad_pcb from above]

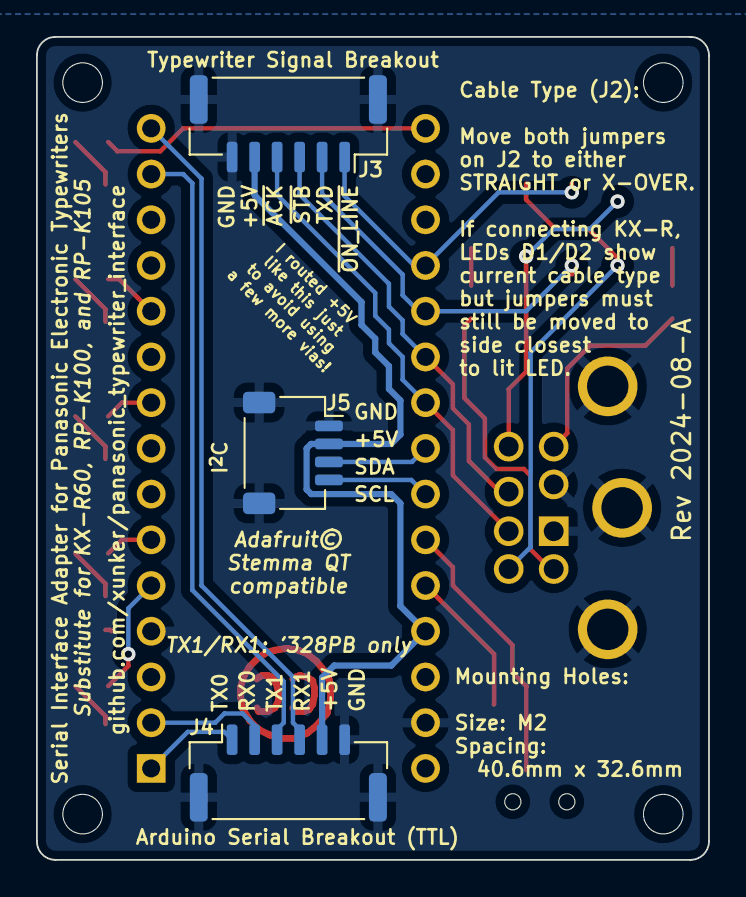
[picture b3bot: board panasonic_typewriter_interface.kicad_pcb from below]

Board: 2 copper layers, 37.3 x 45.7 mm, 27 parts (3 on the bottom side), 30 nets.

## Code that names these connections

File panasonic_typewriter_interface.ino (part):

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/*
ENABLE_MODE_BUTTON

Enables a button connected to MODE_PIN, behaviour defined in mode_button.h */
#define ENABLE_MODE_BUTTON

/*
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// #define ENABLE_DEBUGGING

/* Pin Assignments, To/From Typewriter */
#define ON_LINE_PIN A0 // Output, active LOW
#define STB_PIN     A2 // Output, active LOW
#define ACK_PIN     A3 // Input, active LOW
#define TXD_PIN     A1 // Output; HIGH = 1, LOW = 0

/* Pin Assignments, Switches and Buttons on this device */
#define GO_PIN A6 // trigger printing to begin when this is pulled low
#define MODE_PIN A7 // See mode_button.h

/*
  Pin Assignments, Optional extra LEDs, Enabled by default
  Disabled by commenting-out `#define ENABLE_MULTIPLE_LEDS` below */
#define ON_LINE_LED 8
#define STB_LED     6
#define ACK_LED     2
#define TXD_LED     3

#ifndef LED_BUILTIN
  #define LED_BUILTIN 13
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/*
ENABLE_RTS_CTS

Enable hardware flow control via RTS/CTS Pins. On Arduino Nano and similar, this
_requires_ using an external TTL-serial-to-usb converter which exposes the RTS
and CTS pins because those pins are not connected on the on-board
FT232/CH340/CH9340 ICs.

If you do not use hardware flow control, you *must* add some kind of
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is only half the speed of 30 baud. */
// #define ENABLE_RTS_CTS

#define RTS_PIN 12 // incoming from RTS, active low (for ENABLE_RTS_CTS)
#define CTS_PIN 11 // outgoing to CTS, active low   (for ENABLE_RTS_CTS)

/*
FLOW_STOP_THRESHOLD
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void toggleLED() { togglePin(LED_BUILTIN); }

void setOnLinePin(bool pinState) {
  digitalWrite(ON_LINE_PIN, pinState);
  onLineLed(!pinState); // Signal is Active Low
}
void setSTBPin(bool pinState) {
  digitalWrite(STB_PIN, pinState);
  STBLed(!pinState); // Signal is Active Low
}

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
#ifdef ENABLE_RTS_CTS
  void stopFlow() {
    digitalWrite(CTS_PIN, HIGH);
    flowStopped = true;
    StatusLed(LOW);
  }

  void startFlow() {
    digitalWrite(CTS_PIN, LOW);
    flowStopped = false;
    StatusLed(HIGH);
  }
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  #ifdef ENABLE_DEBUGGING
    uint8_t waitCounter = 0;
  #endif
  while(digitalRead(ACK_PIN) == !pinState) {
    #ifdef ENABLE_DEBUGGING
      if (waitCounter++ >= 100) {
        debug(millis());
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}

bool inRunMode() {
  return (digitalRead(GO_PIN) == LOW);
}

bool inHaltMode() {
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  pinMode(LED_BUILTIN, OUTPUT);

  // Pin Modes for typewriter
  pinMode(ON_LINE_PIN, OUTPUT);
  pinMode(STB_PIN, OUTPUT);
  pinMode(ACK_PIN, INPUT_PULLUP);
  pinMode(TXD_PIN, OUTPUT);
  pinMode(GO_PIN, INPUT_PULLUP);

  // Set initial pin states for good measure
  setOnLinePin(HIGH);
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  StatusLed(LOW);

  #ifdef ENABLE_RTS_CTS
    pinMode(RTS_PIN, INPUT_PULLUP);
    pinMode(CTS_PIN, OUTPUT);

    startFlow();
  #endif
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
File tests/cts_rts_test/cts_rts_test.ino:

/*

Test data string to send: "111111111111111111111111111111111111111111111."

*/

#define RTS_PIN 12 // incoming from RTS, active low
#define CTS_PIN 11 // outgoing to CTS, active low
#define DTR_PIN 10 // incoming from DTR, active low
#define DSR_PIN 9 // outgoing to DSR, active low (labelled "RSD" on my adapter)

void setup() {
  pinMode(LED_BUILTIN, OUTPUT);
  digitalWrite(LED_BUILTIN, LOW);

  pinMode(RTS_PIN, INPUT_PULLUP);
  pinMode(CTS_PIN, OUTPUT);
  digitalWrite(CTS_PIN, LOW);

  pinMode(DTR_PIN, INPUT_PULLUP);
  pinMode(DSR_PIN, OUTPUT);
  digitalWrite(DSR_PIN, LOW);

  Serial.begin(1200);
}

uint8_t charsRecvBeforePause = 0;
uint8_t charsRecvAfterPause = 0;
uint8_t sendPauseAt = 30;
bool pauseSent = false;

void loop() {
  // current = millis();

  // if (current > nextReport) {
  //   nextReport = current + 10000;
  //   Serial.print("RTS: ");
  //   Serial.print(digitalRead(RTS_PIN));
  //   Serial.print(", DTR: ");
  //   Serial.println(digitalRead(DTR_PIN));
  // }

  while( Serial.available() > 0 ) {
    char incomingByte = Serial.read();
    digitalWrite(LED_BUILTIN, !digitalRead(LED_BUILTIN));
    // Serial.print(incomingByte);
    // Serial.print(" 0x");
    // Serial.println(incomingByte, HEX);

    if (incomingByte == '.') {
      Serial.print("charsRecvBeforePause: "); Serial.println(charsRecvBeforePause);
      Serial.print("charsRecvAfterPause: "); Serial.println(charsRecvAfterPause);
      break;
    }

    if (pauseSent) {
      charsRecvAfterPause++;
    } else {
      charsRecvBeforePause++;
    }

    if ((!pauseSent) && (charsRecvBeforePause >= sendPauseAt)) {
      digitalWrite(CTS_PIN, HIGH);
      digitalWrite(DSR_PIN, HIGH);
      Serial.println("Limit reached");
      pauseSent = true;
    }
  }
}

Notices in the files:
adapter_board/panasonic_typewriter_interface/panasonic_typewriter_interface.kicad_pcb:
Board ©️2024
CC BY-NC-SA 4.0
adapter_boards/panasonic_typewriter_interface_v2/panasonic_typewriter_interface_v2.kicad_pcb:
Board ©️2025
